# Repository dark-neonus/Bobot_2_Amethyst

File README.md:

# Bobot_2_Amethyst
Second robot from Bobot series of robots. A huge amount of things in this robot address problems of previous Bobot.

## Table of Contents

- [Features](#features)
  - [Mechanical](#mechanical)
    - [Handle](#handle)
    - [Back Buttons](#back-buttons)
    - [Power Switch](#power-switch)
    - [Screwdriver With Built In Case](#screwdriver-with-built-in-case)
    - [Access panel](#access-panel)
  - [Hardware](#hardware)
    - [Shortcut Components List](#shortcut-components-list)
    - [ESP32 Microcontroller](#esp32-microcontroller)
    - [2.42 Inch OLED I2C Display](#242-inch-oled-i2c-display)
    - [MAX98357A Audio Module](#max98357a-audio-module)
    - [Li-Po 3000mAh 3.7V Battery 1S2P](#li-po-3000mah-37v-battery-1s2p)
    - [BQ25895 Battery Management Module](#bq25895-battery-management-module)
    - [Button Board Based On MCP23017 I/O Expander](#button-board-based-on-mcp23017-io-expander)
    - [Touch Board Based On MPR121QR2 Touch Controller](#touch-board-based-on-mpr121qr2-touch-controller)
  - [Software](#software)
    - [Assets](#assets)
    - [Developer Tools](#developer-tools)
    - [Graphic Engine](#graphic-engine)

# Features 

## Mechanical

### Handle

#### Description

On the top there is the handle which is hidden in base.
It rotates out on bearings.
Rotation is locked by mechanism on top of base.

### Back Buttons

#### Description

On the back there are 9 buttons to interact with bobot.
They are with 3d printed tops with symbols representing purpose.

Buttons:
```
 _________________________________
|    Back    |  Up  |     UI      |
|____________|______|_____________|
|    Left    |  OK  |    Right    |
|____________|______|_____________|
|  Settings  | Down |    Debug    |
|____________|______|_____________|
```

### Power Switch

#### Description

At the bottom of left side of bobot(looking at their face) there is power switch, which is connect batteries to power regulation module.

### Screwdriver With Built In Case

#### Description

At the left side of bobot there is case with screwdriver which can unscrew all screws in bobot.
It is based on push latch mechanism, to be held inside of bobot.

### Access panel

#### Description

At the right side there is panel on 2 screws which give access to main microcontroller esp32 dev kit board. When this panel taken apart, esp32 can be fully removed from socket and access to micro sd is revealed.

## Hardware

### Shortcut Components List

| Component | Quantity| Description | Datasheet | Store |
|-------------|-------|-------------|------------|-------------|
|ESP32 unnamed DevKit board|1|Microcontroller|-|-|
|BQ25895 | 1 | power managment ic | [datasheet](https://www.ti.com/lit/ds/symlink/bq25895.pdf) | [store](https://www.aliexpress.com/item/1005008068013158.html) |
| MCP23017 | 1 | 16-Bit I/O Expander with Serial Interface(16 parallel pins to I2C) | [datasheet](https://ww1.microchip.com/downloads/en/devicedoc/20001952c.pdf) | [store](https://www.aliexpress.com/item/1005006974304942.html) |
| MPR121QR2  | 1 | 12 touch buttons driver with I2C interface | [datasheet](https://files.seeedstudio.com/wiki/Grove-I2C_Touch_Sensor/res/Freescale_Semiconductor;MPR121QR2.pdf) | [store](https://www.aliexpress.com/item/1005006944721047.html) |
| TL2285OA  | 9 | Push latch button without fixation | [datasheet](https://www.alldatasheet.com/html-pdf/437236/E-SWITCH/TL2285OA/385/1/TL2285OA.html) | [store](https://www.aliexpress.com/item/1005006775951751.html) |
| MAX98357A | 2 | Chip for audio output: DAC + amplifier in one chip | [datasheet](https://www.analog.com/media/en/technical-documentation/data-sheets/max98357a-max98357b.pdf) | [store](https://www.aliexpress.com/item/1005010444800168.html) |
| BMI160 | 1 | Sensor gyroscope + accelerometer 6DOF | - | [store](https://www.aliexpress.com/item/1005009421405155.html) |

| Component | Quantity| Store |
|-------------|-------|-------------|
|Resistor 150Ω|1|[store](https://www.aliexpress.com/item/1005008789698065.html)|
|Resistor 4.7kΩ|6|[store](https://www.aliexpress.com/item/1005008789698065.html)|
|Resistor 5.1kΩ|1|[store](https://www.aliexpress.com/item/1005008789698065.html)|
|Resistor 10kΩ|18|[store](https://www.aliexpress.com/item/1005008789698065.html)|
|Resistor 33kΩ|1|[store](https://www.aliexpress.com/item/1005008789698065.html)|
|Resistor 75kΩ|1|[store](https://www.aliexpress.com/item/1005008789698065.html)|
|Capacitor 47nF|1|[store](https://www.aliexpress.com/item/1005010516436707.html)|
|Capacitor 100nF|2|[store](https://www.aliexpress.com/item/1005010516436707.html)|
|Capacitor 1uF|10|[store](https://www.aliexpress.com/item/1005010516436707.html)|
|Capacitor 4.7uF|1|[store](https://www.aliexpress.com/item/1005010516436707.html)|
|Capacitor 10uF|4|[store](https://www.aliexpress.com/item/1005010516436707.html)|
|Inductor 2.2uH|1|[store](https://www.aliexpress.com/item/1005001699576419.html)|
|Thermistor B3435 MF52D 10K|1|[store](https://www.aliexpress.com/item/1005006804356266.html)|

### ESP32 Microcontroller

#### Description

Main microcontroller will be unnamed clone of esp32 wroom dev kit with `30 pins`.
It will be placed in sockets on pcb on right side of bobot.

#### Links

[Overview](https://www.espboards.dev/esp32/esp32-30pin-devkit-generic/)

[Datasheet](https://documentation.espressif.com/esp32_datasheet_en.pdf)

[Technical Reference Manual](http://documentation.espressif.com/esp32_technical_reference_manual_en.pdf)

### 2.42 Inch OLED I2C Display

#### Description

There is 2.42 inch OLED display in front side of bobot.
Esp32 communicate with display using `i2c` protocol on
esp32 dedicated i2c pins. This display use SSD1309 driver.

#### Pinout

| Pin / Signal | Source / Connection | GPIO / Net | Description |
|-------------|---------------------|------------|-------------|
| SDA | ESP32 | GPIO21 | I²C data line (main I²C bus) |
| SCL | ESP32 | GPIO22 | I²C clock line (main I²C bus) |

#### Links

[General information](https://turkish.chenghaolcd.com/doc/44205281/2-42-oled-display-module-ic-i2c-spi-serial-with-ssd1309-controller.pdf)

### MAX98357A Audio Module

#### Description

Bobot uses two MAX98357A modules for stereo audio output. Each module integrates a DAC and Class D amplifier. One module is strapped for left channel, the other for right channel. The modules communicate with ESP32 via shared I2S bus.

#### Configurations

Hardware:

1. Left channel module: GAIN <mark>CONNECTION_TBD</mark> and <span style="text-decoration:overline">SD_MODE</span> strapped to VCC for left channel output
2. Right channel module: GAIN <mark>CONNECTION_TBD</mark> and <span style="text-decoration:overline">SD_MODE</span> strapped to GND for right channel output
3. Both modules share common I2S data and clock lines
4. 1 µF decoupling capacitor between VDD and GND for each module

Software:

1. Configure ESP32 I2S peripheral in stereo mode
2. Set sample rate to <mark>SAMPLE_RATE_TBD</mark> and bit depth to <mark>BIT_DEPTH_TBD</mark>

#### Pinout

| Pin / Signal | Connection | Net / GPIO | Description |
|-------------|------------|------------|-------------|
| LRC (LRCLK) | ESP32 | GPIO27 | I²S word select (left/right clock); shared between both modules. |
| BCLK | ESP32 | GPIO26 | I²S bit clock; shared between both modules. |
| DIN | ESP32 | GPIO25 | I²S serial data input; shared between both modules. |
| GAIN | Configured per module | — | Gain setting pin; sets output gain. |
| <span style="text-decoration:overline">SD_MODE</span> | Configured per module | — | Channel select: left or right. |
| VDD | 3.3V | 3.3V | Power supply (2.5-5.5V); 1 µF decoupling to GND. |
| GND | Ground | GND | Ground. |

#### Links

[Datasheet](https://www.analog.com/media/en/technical-documentation/data-sheets/max98357a-max98357b.pdf)

### Li-Po 3000mAh 3.7V Battery 1S2P

#### Description

There are two parallely connecteed li-po battery in bobot, which in total give 6000mAh battery capacity.

#### Links

[Buy](https://prom.ua/ua/p2843472521-litij-polimernyj-akkumulyator.html)

### BQ25895 Battery Management Module

#### Description

Bobot have power management module, which will consist of: 
- `BQ25895` I2C Controlled Single Cell 5-A Fast Charger with MaxChargeTM for High Input
Voltage and Adjustable Voltage 3.1-A Boost Operation
- Thermistor as BQ25895 requires placed onto battery with
  RTHcold = 27 kΩ at 0 °C
  and RTHhot = 4.9 kΩ at 45 °C values
- Led to indicate charge status
- Connection to esp32 I2C bus and INT pin support

And will do:
- Active conversation with Esp32 with transfering measurements of voltages and current(battery monitor feature)

#### Configurations

Hardware:

1. CE pin tied to GND to enable charging
2. Using resistors RT1=5.1 kΩ and RT2=33 kΩ to make BQ25895 read thermistor values correct
3. Led going from SYS to STAT through 2.2kΩ resistor
4. Connecting ILIM pin to GND through Rilim=150 Ω resistor. Calculated using formula from datasheet at section 8.2.12. 150 Ω resistor limit input current to ~2.6A.
5. OTG pin connected to GND to disable boost mode activation

Software:

1. Set register CONV_RATE to 1 to enable active conversation between BQ25895 and ESP32
2. <mark>Set register IINLIM to value representing \<DESIRED_INPUT_CURRENT>
3. <mark>Set TREG to \<DESIRED_MAXIMAL_IC_TEMPERATURE> to regulate at which temperature BQ25895 will lower down charging current

#### Pinout

| Pin / Signal | Connection | Net / GPIO | Description |
|-------------|------------|------------|-------------|
| SDA | ESP32 | GPIO21 | I²C data line for charger configuration/monitoring. |
| SCL | ESP32 | GPIO22 | I²C clock line for charger configuration/monitoring. |
| INT | ESP32 | GPIO (TBD) | Open-drain interrupt (active-low) for charge/fault events; 10 kΩ pull-up to 3.3 V. |
| VBUS | USB Type-C port | VBUS | Charger input supply (3.9–14 V). Decouple close to pin. |
| D+ | USB only | Connect only to USB connector | Used internally for BC1.2/MaxCharge detection. |
| D− | USB only | Connect only to USB connector | Same as D+. |
| STAT | Status LED | — | Open-drain charge status output; LED + resistor to 3.3 V. |
| TS | NTC divider | NTC | Battery temperature sense via NTC near battery; safety-critical. |
| BAT | Battery pack | BAT+ | Battery positive terminal (1S Li-ion/Li-poly). |
| SYS | System rail | SYS | Managed system supply; feeds 3.3 V regulator for ESP32. |
| PGND | Power ground | GND | High-current ground return for charger, battery, SYS, PMID caps. |
| CE | GND | — | Charge enable (active-low); tied to GND for always-enabled charging. |
| ILIM | Resistor → GND | R_ILIM | Hardware input-current limit set to ~3 A (protects USB source). |
| SW | Inductor | SW | Switching node to inductor (keep short, noisy). |
| BTST | Bootstrap cap | BTST | Bootstrap capacitor to SW for high-side gate drive. |
| REGN | Decoupling cap | REGN | Internal LDO output; bias rail (decouple to GND). |
| EPAD (PowerPAD) | PCB copper | PGND | Thermal + electrical ground; must be soldered to PGND with vias. | 
| OTG | Disabled | Tie to GND | Prevents boost (OTG) mode activation. |
| PMID | Not exported | Local ceramic caps to PGND only (≥8.2 µF) | Do not power loads; keep short return. |
| QON | Unused | Leave unconnected | Internal pull-up keeps default behavior. |
| DSEL | Unused | Leave unconnected | Not needed without external USB data switch. |

### Button Board Based On MCP23017 I/O Expander

#### Description

The MCP23017 is a 16-bit I/O expander used to interface with the 9 back panel buttons. It communicates with the ESP32 via I2C at address <mark>I2C_ADDRESS_TBD</mark>. The device provides interrupt-on-change functionality through its INTA and INTB pins, allowing the ESP32 to detect button presses efficiently without constant polling.

Buttons:
```
 _________________________________
|    Back    |  Up  |     UI      |
|____________|______|_____________|
|    Left    |  OK  |    Right    |
|____________|______|_____________|
|  Settings  | Down |    Debug    |
|____________|______|_____________|
```

#### Configurations

Hardware:

1. I2C address set via A0, A1, A2 pins: <mark>ADDRESS_CONFIG_TBD</mark>
2. INTA and INTB pins pulled up to 3.3V through 4.7 kΩ resistors
3. NOT RESET pin tied to 3.3V to keep device enabled
4. Each button input uses a low-pass filter with:
   - 10 kΩ pull-up resistor to 3.3V (default state: logic HIGH)
   - 10 kΩ series resistor between button and IC pin
   - 1 µF capacitor to GND for debouncing
5. Buttons are in high-Z state (disconnected) by default, connect to GND when pressed (active-low)

Software:

1. Configure GPA0-GPA7 and GPB0 as inputs with interrupt-on-change enabled
2. Set up interrupt polarity and configure interrupt mirroring if needed

#### Pinout

| Pin / Signal | Connection | Net / GPIO | Description |
|-------------|------------|------------|-------------|
| SDA | ESP32 | GPIO21 | I²C data line (shared with display and BMS). |
| SCL | ESP32 | GPIO22 | I²C clock line (shared with display and BMS). |
| INTA | ESP32 | <mark>GPIO (TBD)</mark> | Interrupt output for Port A changes; 4.7 kΩ pull-up to 3.3V. |
| INTB | ESP32 | <mark>GPIO (TBD)</mark> | Interrupt output for Port B changes; 4.7 kΩ pull-up to 3.3V. |
| RESET | 3.3V | — | Active-low reset; tied to 3.3V to keep device enabled. |
| A0 | <mark>TBD</mark> | — | I²C address bit 0. |
| A1 | <mark>TBD</mark> | — | I²C address bit 1. |
| A2 | <mark>TBD</mark> | — | I²C address bit 2. |
| GPA0 | BTN_BACK | — | Back button input (filtered, active-low). |
| GPA1 | BTN_TOP | — | Up button input (filtered, active-low). |
| GPA2 | BTN_UI | — | UI button input (filtered, active-low). |
| GPA3 | BTN_LEFT | — | Left button input (filtered, active-low). |
| GPA4 | BTN_OK | — | OK button input (filtered, active-low). |
| GPA5 | BTN_RIGHT | — | Right button input (filtered, active-low). |
| GPA6 | BTN_SETTINGS | — | Settings button input (filtered, active-low). |
| GPA7 | BTN_DOWN | — | Down button input (filtered, active-low). |
| GPB0 | BTN_DBG | — | Debug button input (filtered, active-low). |
| GPB1-GPB7 | Unused | — | Available for future expansion. |
| VSS | GND | GND | Ground. |
| VDD | 3.3V | 3.3V | Power supply (1.8-5.5V). |

### Touch Board Based On MPR121QR2 Touch Controller

#### Description

The MPR121QR2 is a 12-channel capacitive touch sensor controller used to implement a touch-sensitive electrode matrix. It communicates with the ESP32 via I2C at address <mark>I2C_ADDRESS_TBD</mark>. The device provides interrupt functionality through its NOT IRQ pin, allowing the ESP32 to detect touch events efficiently.

The electrode matrix follows the design from [NXP Application Note AN4600](https://www.nxp.com/docs/en/application-note/AN4600.pdf), where touch detection is achieved by the intersection of X and Y electrodes:
- ELE0-ELE6 correspond to X0-X6 positions (7 columns)
- ELE7-ELE11 correspond to Y0-Y4 positions (5 rows)

Touch coordinates are determined by the intersection of active XN and YM electrodes.

#### Configurations

Hardware:

1. I2C address set via ADD pin: <mark>ADDRESS_CONFIG_TBD</mark>
2. NOT IRQ pin pulled up to 3.3V through 4.7 kΩ resistor
3. REXT pin pulled down through 75 kΩ resistor to GND
4. 0.1 µF decoupling capacitor between VDD and VSS
5. 0.1 µF capacitor between VREG and GND for internal regulator stability
6. PCB electrode layout follows AN4600 routing guidelines
7. Electrode pad size: 5 mm × 5 mm (increased from AN4600's 3.5-4 mm recommendation)

Software:

1. <mark>Configure touch and release thresholds for each electrode</mark>
2. <mark>Enable electrode matrix scanning mode according to AN4600</mark>
3. <mark>Implement touch coordinate decoding from electrode intersections</mark>

#### Pinout

| Pin / Signal | Connection | Net / GPIO | Description |
|-------------|------------|------------|-------------|
| SDA | ESP32 | GPIO21 | I²C data line (shared with display, BMS, and button board). |
| SCL | ESP32 | GPIO22 | I²C clock line (shared with display, BMS, and button board). |
| IRQ | ESP32 | <mark>GPIO (TBD)</mark> | Active-low interrupt output for touch events; 4.7 kΩ pull-up to 3.3V. |
| ADD | <mark>TBD</mark> | — | I²C address selection pin. |
| ELE0 | Touch electrode | X0 | Electrode column 0. |
| ELE1 | Touch electrode | X1 | Electrode column 1. |
| ELE2 | Touch electrode | X2 | Electrode column 2. |
| ELE3 | Touch electrode | X3 | Electrode column 3. |
| ELE4 | Touch electrode | X4 | Electrode column 4. |
| ELE5 | Touch electrode | X5 | Electrode column 5. |
| ELE6 | Touch electrode | X6 | Electrode column 6. |
| ELE7 | Touch electrode | Y0 | Electrode row 0. |
| ELE8 | Touch electrode | Y1 | Electrode row 1. |
| ELE9 | Touch electrode | Y2 | Electrode row 2. |
| ELE10 | Touch electrode | Y3 | Electrode row 3. |
| ELE11 | Touch electrode | Y4 | Electrode row 4. |
| REXT | 75 kΩ → GND | — | External resistor for charge current setting. |
| VREG | 0.1 µF cap → GND | — | Internal regulator output; decoupled to GND. |
| VSS | GND | GND | Ground. |
| VDD | 3.3V | 3.3V | Power supply (1.71-3.6V); 0.1 µF decoupling to GND. |

#### Links

[Application Note AN4600 - MPR121 Proximity Sensing](https://www.nxp.com/docs/en/application-note/AN4600.pdf)

## Software

### Assets

#### Description

There will be 4 main face assets libraries(profiles) where each of them can be set as source library, single library with faces not
connected to any library and few non-main libraries which
may be added in future for Bobot:

1. Classic - face library of first Bobot with possible extensions for new features
2. Amethyst - face library for current model which will stick to classic expressions but with fresh look
3. Cutie - face library consisting of cute assets with cat-like features and big eyes
4. Doodles - face library consisting of weirdly paint assets representing scratch style
4. Other - library with face expressions not connected to any full library, cannot be set as source library

#### Structure

##### Expression

Expression - elementary unit of Bobot expressions graphic. It is directory with graphic assets of expression nd file with expression description and metadata. Expression can be set as temporally Bobot face in mode with manual expression selection.

Expression strucutre:

```
Expression
├── Description.ini
├── Frames
│   ├── Frame_00.bin
│   ├── Frame_01.bin
│   ├──...
│   ├── Frame_N.bin
```

Frame binary format:
Each frame file is binary file with monochrome bitmap data optimized for u8g2 library. Frame dimensions are stored in Description.ini to reduce file size and improve loading speed. Format structure: monochrome bitmap data where each byte represents 8 vertical pixels organized in column-major order. During runtime dimensions are read once from Description.ini, then frames are read from SD card and passed directly to u8g2 display functions.

Expression `Description.ini`:
```ini
; Description for Expression_Name expression

[Loop]
; Supported Loop types:
;
; 1. IdleBlink(default) - Display first frame for random time in range
;                           [IdleTimeMinMS, IdleTimeMaxMS] ms and after that
;                           run animation with AnimationFPS fps.
;                           After that switch frame to first and repeat.
;
; 2. Loop - Repeat animation from first frame to last with AnimationFPS fps.
;           IdleTimeMinMS and IdleTimeMaxMS are unnecessary and wiil be ignored
;           if presented
;
; 3. Image - Display only first frame. All fields except type are unnecessary 
;             and wiil be ignored if presented

; Type field must be first
Type = IdleBlink ; default = IdleBlink
AnimationFPS = 20 ; default = 20
IdleTimeMinMS = 1000 ; default = 1000
IdleTimeMaxMS = 1000 ; default = 1000

[Dimensions]
; Frame dimensions (auto-filled by export tool)
Width = 128
Height = 64
```

##### Library
Library - list of expressions. Some libraries can be sourced to be used as Bobot faces for corresponding events. Library consist of file with library description, information and metadata, directory with expressions and file with behaviour and mapping(if needed) expressions in expressions directory to Bobots events. If there is no behaviour and mapping file, library cant be sourced.
```
Library
├── Description.ini
├── Behaviour.csv
├── Expressions
│   ├── Expression_A
│   ├── Expression_B
│   ├──...
│   ├── Expression_Z
```

### Developer Tools

#### Graphics Structure Generation Script
Script is placed in `devtools` directory under project root. It consists of two files: `generate_graphics_structure.py` with main logic and `generate_graphics.sh` shell wrapper for convenient execution. Script can be run with `./devtools/generate_graphics.sh` from project root.

Script reads `assets/graphics/Description.ini` and processes all libraries marked as `true`. For each enabled library it creates directory structure in `assets/graphics/libraries/LibraryName` if not exists. Then it iterates over all directories inside library which are expressions. For each expression it generates default `Description.ini` if not present.

For expressions containing `.aseprite` or `.ase` files script uses aseprite in batch mode to export animation frames as PNG sequence into temporary directory. Then it converts each PNG frame to u8g2-compatible binary format and saves as `Frame_XX.bin` files in expression `Frames` subdirectory. After conversion all temporary PNG files are deleted. If `Frames` directory exists from previous run it is completely cleared before generating new frames to avoid stale data.

Aseprite is built from source during Docker container setup and available at `/usr/local/bin/aseprite`. Script automatically finds aseprite executable and falls back gracefully if not available.

#### SD Card Assets Update Script
**WARNING: Currently this feature is broken and dont work properly**

##### ESP32 Side
ESP32 can enter asset upload mode when requested, hosting a simple HTTP server on WiFi. In main microcontroller loop it checks for button combination or serial command to activate upload mode. When activated, ESP32:
- Stops regular operating mode
- Starts HTTP server on port 8080
- Waits for upload requests

Upload process:
1. HTTP POST to `/start` - ESP32 deletes entire `/assets` directory (preserving other files/directories)
2. HTTP POST to `/file` - Upload individual files with path in request
3. HTTP POST to `/complete` - Finalize upload and return to normal mode

The `/assets` directory is completely cleared at start of upload, but other directories and files on SD card remain untouched. Upload mode cannot be interrupted except by system-level events.

##### Host (PC) Side
Host PC connects to ESP32 via WiFi to upload assets. In `devtools` directory there are `flash_micro_sd.sh` and `flash_micro_sd.py` scripts:

**Shell script (`flash_micro_sd.sh`)**:
- Manages directory navigation
- Configures Python environment
- Provides simple interface: `./devtools/flash_micro_sd.sh`

**Python script (`flash_micro_sd.py`)**:
- Discovers ESP32 on network (mDNS or manual IP)
- Sends `/start` command and waits for confirmation
- Uploads entire `assets` directory via HTTP POST (excludes .aseprite files)
- Sends `/complete` command when done
- Displays progress and handles errors

Usage:
```bash
# From project root
./devtools/flash_micro_sd.sh

# Or with custom IP
./devtools/flash_micro_sd.sh --ip 192.168.1.100
```

The upload is reliable (checksums verified), fast (WiFi bandwidth), and doesn't interfere with USB console/debugging.

### Servo Control

Bobot uses PCA9685 16-channel PWM driver (default I2C address 0x40) to control servo motors for legs. Driver supports up to 16 servos with angle control from 0 to 180 degrees. On startup all servos are initialized to 90 degrees center position.

A servo control UI mode is available for testing and calibration. Mode is accessed by cycling through UI modes with UI button. In servo mode:
- LEFT/RIGHT buttons switch between channels 0-15
- UP/DOWN buttons adjust selected servo angle in 5-degree increments
- Display shows current channel and angle

### Graphic Engine

#### Position class Vec2i

Class which will hold two integer values x and y and whcih will be used for working with position values.
This class will have implementation of basic operaions: addition, substraction, multiplicating, their with assignment analogues(e.g. plus equal) and negative sign.
Also it will have functions which will return string that represents vector data.
This class will be used to hold values like positions, offset, speed, etc.

#### Frame class

Simple class which will hold only bitmap value of frame in format which will be place-and-go for u8g2 function to draw bitmap on screen and frame size.
Class will have function to build object from raw file data, received from storage through DMA.

#### Expression class

Class which will hold sequence of frames, current frame index, fps and data about correct playback way of animation.
This class will have functions to draw current frame on given display with given offset, increment frame index, set frame index, update function which will handle correct index incrementation depended on animation loop type.
Also there will be function to create animation object(which will do subcalls of constructing frames from files) from given directory

#### Future functional
For now this code is just to test code on development setup to understand that prom not in code, when test will be runned on manufactured pcb's. They wont be implemented right now for time saving and simplisity.
Future functional may include, but not limited to:

1) Expression Library class which will handle mapping events/states to storage directories and will handle dynamic load of expression on event/state switch(to not hold full expressions library in memory). Also this class can handle graphic profiles switch.

2) Upgrading Expression class functions to work correct in energy efficient code, including handling fps using timer interrupts, to set esp32 to sleep mode for as long as possible.

3) Profile class which will be placeholder for data about each library possibilities, storage path and names.

4) Classes for text, side menu, burger menu, navigation system visualizations, regular bitmaps drawings, and possibly more.

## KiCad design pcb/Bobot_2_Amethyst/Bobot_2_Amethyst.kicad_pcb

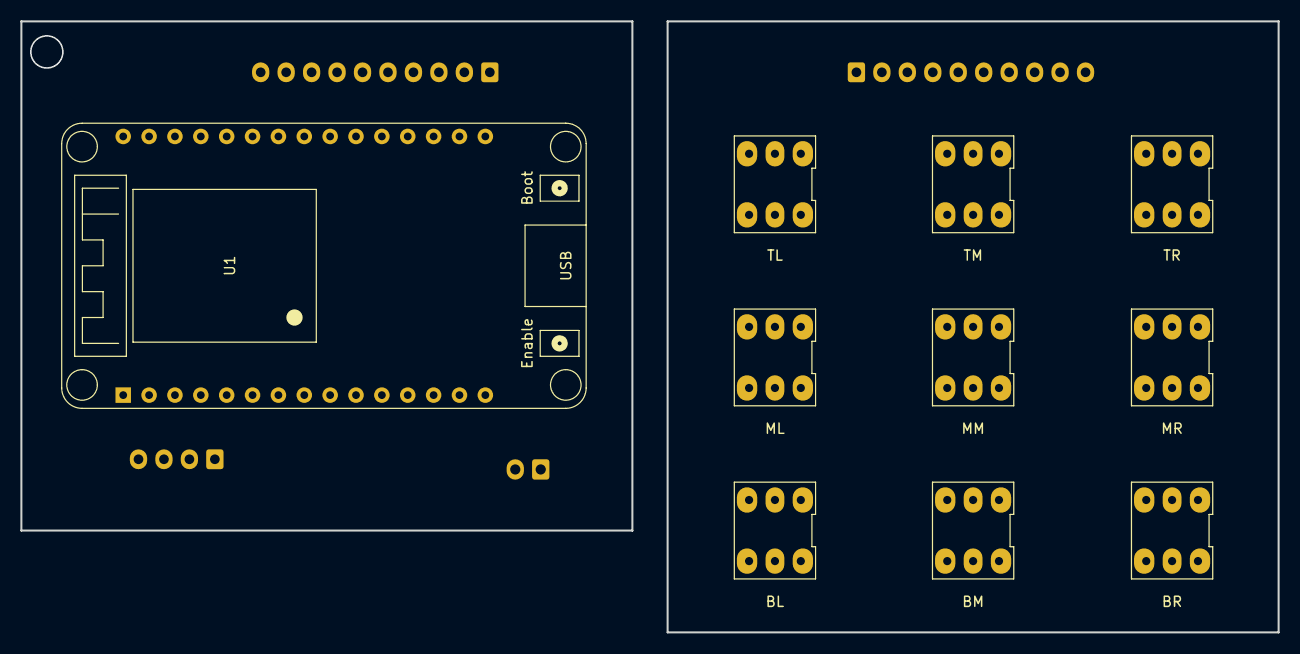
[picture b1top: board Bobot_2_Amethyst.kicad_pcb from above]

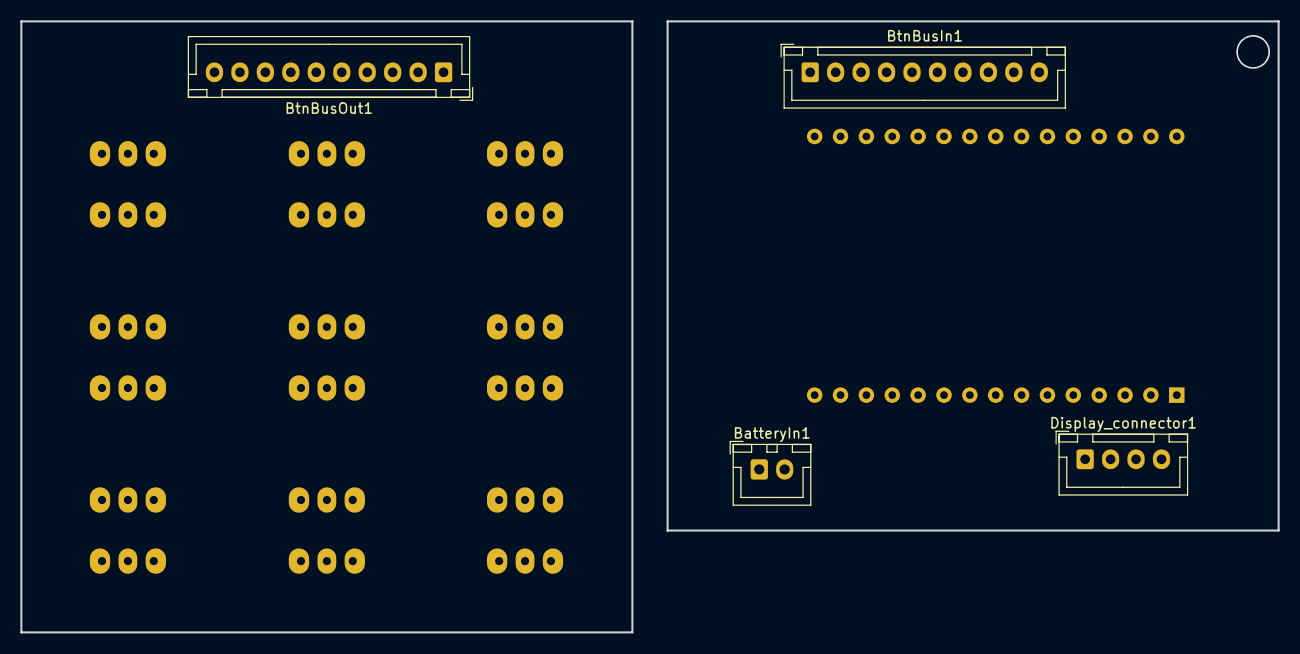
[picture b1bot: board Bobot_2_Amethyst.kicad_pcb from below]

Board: 2 copper layers, 123.5 x 60.0 mm, 14 parts (4 on the bottom side), 20 nets, no tracks yet.

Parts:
BatteryIn1: Conn_01x02_Socket; JST_XH_B2B-XH-A_1x02_P2.50mm_Vertical
BtnBL1: BL; SW_DPDT_XLX
BtnBM1: BM; SW_DPDT_XLX
BtnBR1: BR; SW_DPDT_XLX
BtnBusIn1: BtnBusIn; JST_XH_B10B-XH-A_1x10_P2.50mm_Vertical
BtnBusOut1: BtnBusOut; JST_XH_B10B-XH-A_1x10_P2.50mm_Vertical
BtnML1: ML; SW_DPDT_XLX
BtnMM1: MM; SW_DPDT_XLX
BtnMR1: MR; SW_DPDT_XLX
BtnTL1: TL; SW_DPDT_XLX
BtnTM1: TM; SW_DPDT_XLX
BtnTR1: TR; SW_DPDT_XLX
Display_connector1: Conn_01x04_Socket; JST_XH_B4B-XH-A_1x04_P2.50mm_Vertical
U1: ESP32_DevKit_V1_DOIT; esp32_devkit_v1_doit

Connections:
GND: BatteryIn1.1 (GND), BtnBusIn1.1 (GND), Display_connector1.1 (GND), U1.14 (GND), U1.17 (GND)
GND1: BtnBL1.3 (C), BtnBM1.3 (C), BtnBR1.3 (C), BtnBusOut1.1 (GND), BtnML1.3 (C), BtnMM1.3 (C), BtnMR1.3 (C), BtnTL1.3 (C), BtnTM1.3 (C), BtnTR1.3 (C)
unnamed: BtnBusIn1.8 (BL), U1.25 (IO19)
unnamed: BtnBusIn1.9 (BM), U1.26 (IO21)
unnamed: BtnBusIn1.10 (BR), U1.29 (IO22)
unnamed: BtnBusIn1.5 (ML), U1.22 (IO17)
unnamed: BtnBusIn1.6 (MM), U1.23 (IO5)
unnamed: BtnBusIn1.7 (MR), U1.24 (IO18)
unnamed: BtnBusIn1.2 (TL), U1.18 (IO15)
unnamed: BtnBusIn1.3 (TM), U1.20 (IO4)
unnamed: BtnBusIn1.4 (TR), U1.21 (IO16)
unnamed: BtnBL1.2 (B), BtnBusOut1.8 (BL)
unnamed: BtnBM1.2 (B), BtnBusOut1.9 (BM)
unnamed: BtnBR1.2 (B), BtnBusOut1.10 (BR)
unnamed: BtnBusOut1.5 (ML), BtnML1.2 (B)
unnamed: BtnBusOut1.6 (MM), BtnMM1.2 (B)
unnamed: BtnBusOut1.7 (MR), BtnMR1.2 (B)
unnamed: BtnBusOut1.2 (TL), BtnTL1.2 (B)
unnamed: BtnBusOut1.3 (TM), BtnTM1.2 (B)
unnamed: BtnBusOut1.4 (TR), BtnTR1.2 (B)

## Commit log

2025-10-11 chore: add empty pcb files
2025-10-11 pcb: add basic elements to esp32 and buttons pcbs
2025-10-12 pcb: update buttons alignment
2025-12-17 docs: add base of technical specifications of bobot
2025-12-18 docs: add technical specifications for screwdriver case, esp32, display, batteries and battery management module
2025-12-19 docs: update battery management module pinout
2025-12-20 docs: complete BQ25895, few unfilled placeholder values remains
2025-12-21 pcb: reorganize kicad project and add basic schematics
2025-12-21 pcb: add battery and thermistor connection schematics
2025-12-21 docs: add base of shortcut components list
2025-12-25 pcb: complete BMS board schematic
2025-12-25 docs: update shortcut component list to include BMS required components
2025-12-25 pcb: add buttons board schematics except I2C address
2025-12-25 docs: add components for buttons board into shortcut components list, fix mistakes and fill out some values
2025-12-27 pcb: add touch sensor board
2025-12-28 docs: add documentation for MCP23017 io expander and buttons connection
2025-12-28 docs: add documentation for MPR121QR2 touch controller and touch matrix
2025-12-29 docs: add inertial module and audio chips to shortcut components list
2025-12-30 chore: add basic code structure witth display demo
2025-12-30 chore: swap libraries with just local clones
2025-12-30 fix: change function initializing display driver for right addressing
2025-12-30 feat: add basic working example for display and buttons
2026-01-07 fix: old components bug
2026-01-07 fix: add git submodules as regualr directories with modified code
2026-01-07 feat: add working sd card communication via sdio protocol
2026-01-08 feat: add basic code for bmi160 module
2026-01-10 docs: add graphic docs basics for Expression and Library
2026-01-10 assets: add basic graphic structure and first asset
2026-01-10 chore: update access permissions
2026-01-10 docs: add structure documentation for Description.ini of expressions
2026-01-10 feat: add tools to generate graphics assets from aseprite projects
2026-01-10 assets: add Normal_Positive and Dizzy_1 assets, update assets docs and fix graphics generation script indexing bug
2026-01-12 feat: add micro sd assets flash over wifi
2026-01-13 docs: add graphic engine basic documentation
2026-01-13 feat: add basic graphic engine implementation with Normal_Positive expression test
2026-01-14 fix: fix incorrect frame export order and inversion of pixels
2026-01-14 feat: add debug UI switching between animations on UI press
2026-01-14 feat: add animation imu-based offset
2026-01-14 feat: baddly optimize expression load process
2026-01-14 feat: change image loading implementation and UI button timing
2026-01-17 docs: add documentation for MAX98357A audio module
2026-01-17 featL add unoptimized audio playback support
2026-01-18 feat: add buzzer controll
2026-02-04 feat: add legs control mode
2026-02-06 docs: add design_specs for legs editor
2026-02-06 feat: add gui skeleton for legs editor
2026-02-06 feat: add legs editor gui forwarding into browser
2026-02-06 fix: fix 2d render of robot
2026-02-06 fix: fix 3d view
2026-02-06 fix: legs rendering
2026-02-06 fix: fix small gui mistakes and correct robot dimensions
2026-02-07 refactor: remove i2c bus scanner
2026-02-08 fix: change servo channel order
2026-02-09 feat: add web page controls
2026-02-10 feat: add working stand up and housing sequences for legs
